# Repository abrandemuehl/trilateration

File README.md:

# Attempted ESP8266 Based WiFi Trilateration

This was a project done for UIUC's ECE 445 - Senior Design.

This project does not trilaterate positions succesfully - code for communication is still needed.

The program writes the MAC address and the associated RSSI of packets received in promiscuous mode to the UART connection at 115200 BAUD.
The messages are in a binary format found in `common/messages.h`.
They are read back by the PC program and displayed like so
```
WIFI:   6c:72:e7:d1:12:4d 40
Serial: 6c:72:e7:d1:12:4d 40
WIFI:   6c:72:e7:d1:12:4d 40
Serial: 6c:72:e7:d1:12:4d 40
WIFI:   6c:72:e7:d1:12:4d 40
Serial: 6c:72:e7:d1:12:4d 40
WIFI:   6c:72:e7:d1:12:4d 40
Serial: 6c:72:e7:d1:12:4d 40
WIFI:   6c:72:e7:d1:12:4d 40
Serial: 6c:72:e7:d1:3f:e2 6
WIFI:   6c:72:e7:d1:3f:e2 6
Serial: 6c:72:e7:d1:3f:e2 6
WIFI:   6c:72:e7:d1:3f:e2 6
Serial: 40:78:e7:d1:3f:e2 6
WIFI:   40:78:e7:d1:3f:e2 6
Serial: 2c:78:e7:d1:3f:e2 6
```
Messages prefaced with `WiFi` were received by the incomplete communication code.
The `Serial` came from the ESP8266.

There are some useful code snippets that can be used in other ESP8266 based projects.
The hardware design files also might be somewhat useful for reference.

The original goal of the project was to create a way to track WiFi devices indoors.
Our strategy was to enter promiscuous mode, and look at the RSSI of received packets, and use that to estimate the distance of the transmitting device from the ESP.

Boards were designed as part of the requirements for the class, but they are almost hardware equivalent to most simple ESP modules that you can purchase online for a lower price...
Also, the boards that we created have problems that we couldn't track down. We're pretty sure they were caused by poor fabrication, but there may be some flaw in the original designs.

## Building and running

Note: These instructions are for linux only.
We ran into issues with the toolchain on Mac that had to do with the size of the binary created not fitting into iram.

First, clone with the submodules included
```bash
$ git clone --recursive https://github.com/abrandemuehl/trilateration.git
```
Or, if you've already cloned it without submodules, use
```bash
$ git submodule update --init --recursive
```

Then, edit the makefile for the submodule [esp-open-sdk](https://github.com/pfalcon/esp-open-sdk) to use the 0.9.4 version.
This can be done by editing the line that says
```
VENDOR_SDK = x.x.x
```
to be
```
VENDOR_SDK = 0.9.4
```
then run `make` in the esp/esp-open-sdk directory. (This step takes a while)

Once that is complete, you can build the main app.

First, create a directory to hold the binary files `mkdir esp/bin`.

To build the main application, you first have to `source .env` to get the paths of the toolchain commands.
Once you've done that, run `make` in the `esp` directory.

Then you can run `make flash` to use the esptool to flash it onto the ESP8266 module of your choice that is in program mode.

## Strategy
Trilateration is a pretty simple concept.
You have 3 spheres in space with known radii, and you want to find the intersection point of all of the surfaces of the spheres.
You can use this strategy to get the location of a point, given the centers and radii of 3 spheres where the point lies on their surfaces.

See the [wikipedia](https://en.wikipedia.org/wiki/Trilateration) article and [this stackoverflow question](http://stackoverflow.com/questions/16176656/trilateration-and-locating-the-point-x-y-z) for more information about the algorithm.

The exact trilateration algorithm is implemented in `common/trilatertion.c`.

## ESP Specific Code

#### Promiscuous mode and MAC addresses
In order to use communicate the positions and radii of the circles estimated from the RSSI, each device must be identifiable through some means.
We chose the MAC address of devices, as this is *supposed* to be unique per device.
However, the information given to the promiscuous_rx_cb by the SDK is very limited on SDK versions >= 0.9.5.
It only passes some basic information about the packet to the callback, which does not include anything that can be used to identify the sender.
I'm not sure why they removed this functionality, but it exists in the SDK version 0.9.4, so we chose to use it.

When using SDK 0.9.4, we can get the whole 802.11 header of the packet, making it easy to get the MAC address of the sender and destination devices.
The basic structure of 802.11 packets is shown in `esp/network_80211.h` which we modified from the version found at https://github.com/ly0/esp8266-smartlink.
We added the structure of data frames, since that was what we wanted to use.

#### STATION mode and Promiscuous mode
The big problem we ran into with promiscuous mode was that the ESP must be in STATION mode for promiscuous mode to work.
This was a problem for our original design, since we planned to use the mesh networking capabilities of the ESP to communicate the positions and radii of the circles used for trilateration.

#### `rst cause:4`
Another problem we found was that the promiscuous mode callback runs at a high priority.
So, when you get more packets than you can process, the promiscuous callback will starve some other important task in the SDK (not sure which one) and cause a watchdog timer to reset the device.
The reset will cause the device to write `rst cause:4, boot mode: (x, x)` to the UART connection.
The `cause:4` indicates that the reset was caused by a watchdog timer going off, as documented [here](http://www.esp8266.com/viewtopic.php?p=2096#p2112).

The only way to mitigate this reset problem is to do less work in the promiscuous mode callback.
This doesn't mean you have to do less work total, you just need to delegate it to a lower priority task.

In the ESP sdk, tasks can be defined with the following lines of code
```C
#define message_procTaskPrio        1
#define message_procTaskQueueLen    2
os_event_t message_procTaskQueue[message_procTaskQueueLen];
static void message_procTask(os_event_t *event);

void ICACHE_FLASH_ATTR
user_init() {
  ...
  // Defines a task that can be started with system_os_post
  system_os_task(message_procTask, message_procTaskPrio,
                 message_procTaskQueue, message_procTaskQueueLen);
  ...
}
```

This defines, the task, but doesn't run it.
To run a task, run system_os_post in your promicuous mode callback.
```
void ICACHE_FLASH_ATTR
promisc_cb(uint8_t *buf, uint16_t len) {
  ...
  system_os_post(message_procTaskPrio, 0, 0);
  ...
}
```
When `system_os_post` is called, it will queue up the message processing task to be run once the CPU frees up from all of the system tasks that run at higher priority.

How you pass data to this task is up to you.
I used a ring buffer, but I didn't make it thread safe, so there are race conditions in there.

## PC Code

The PC code was added because of the STATION mode problem with promiscuous mode.
Without access points to connect to, each board would not be able to communicate with the other ones, making trilateration impossible.
We didn't want to require that the devices connect to a network, so we planned to send messages over USB to a laptop, then have the laptop broadcast the values.
We ran out of time before we could test if this method would work.

## Trilateration Problems
The trilateration algorithm and code that we had intended to use would not with real values based on RSSI.
The algorithm solves a system of equations using the spheres, but only finds a solution if they intersect at only one point.
This is not a good algorithm because it doesn't find a solution when the estimated spheres don't exactly line up, which won't happen in almost all cases.

## In conclusion

We ran out of time and couldn't finish the project for the class.
We have no intentions of working on this code again, but if you have any questions about the choices made in the code, feel free to open an issue.

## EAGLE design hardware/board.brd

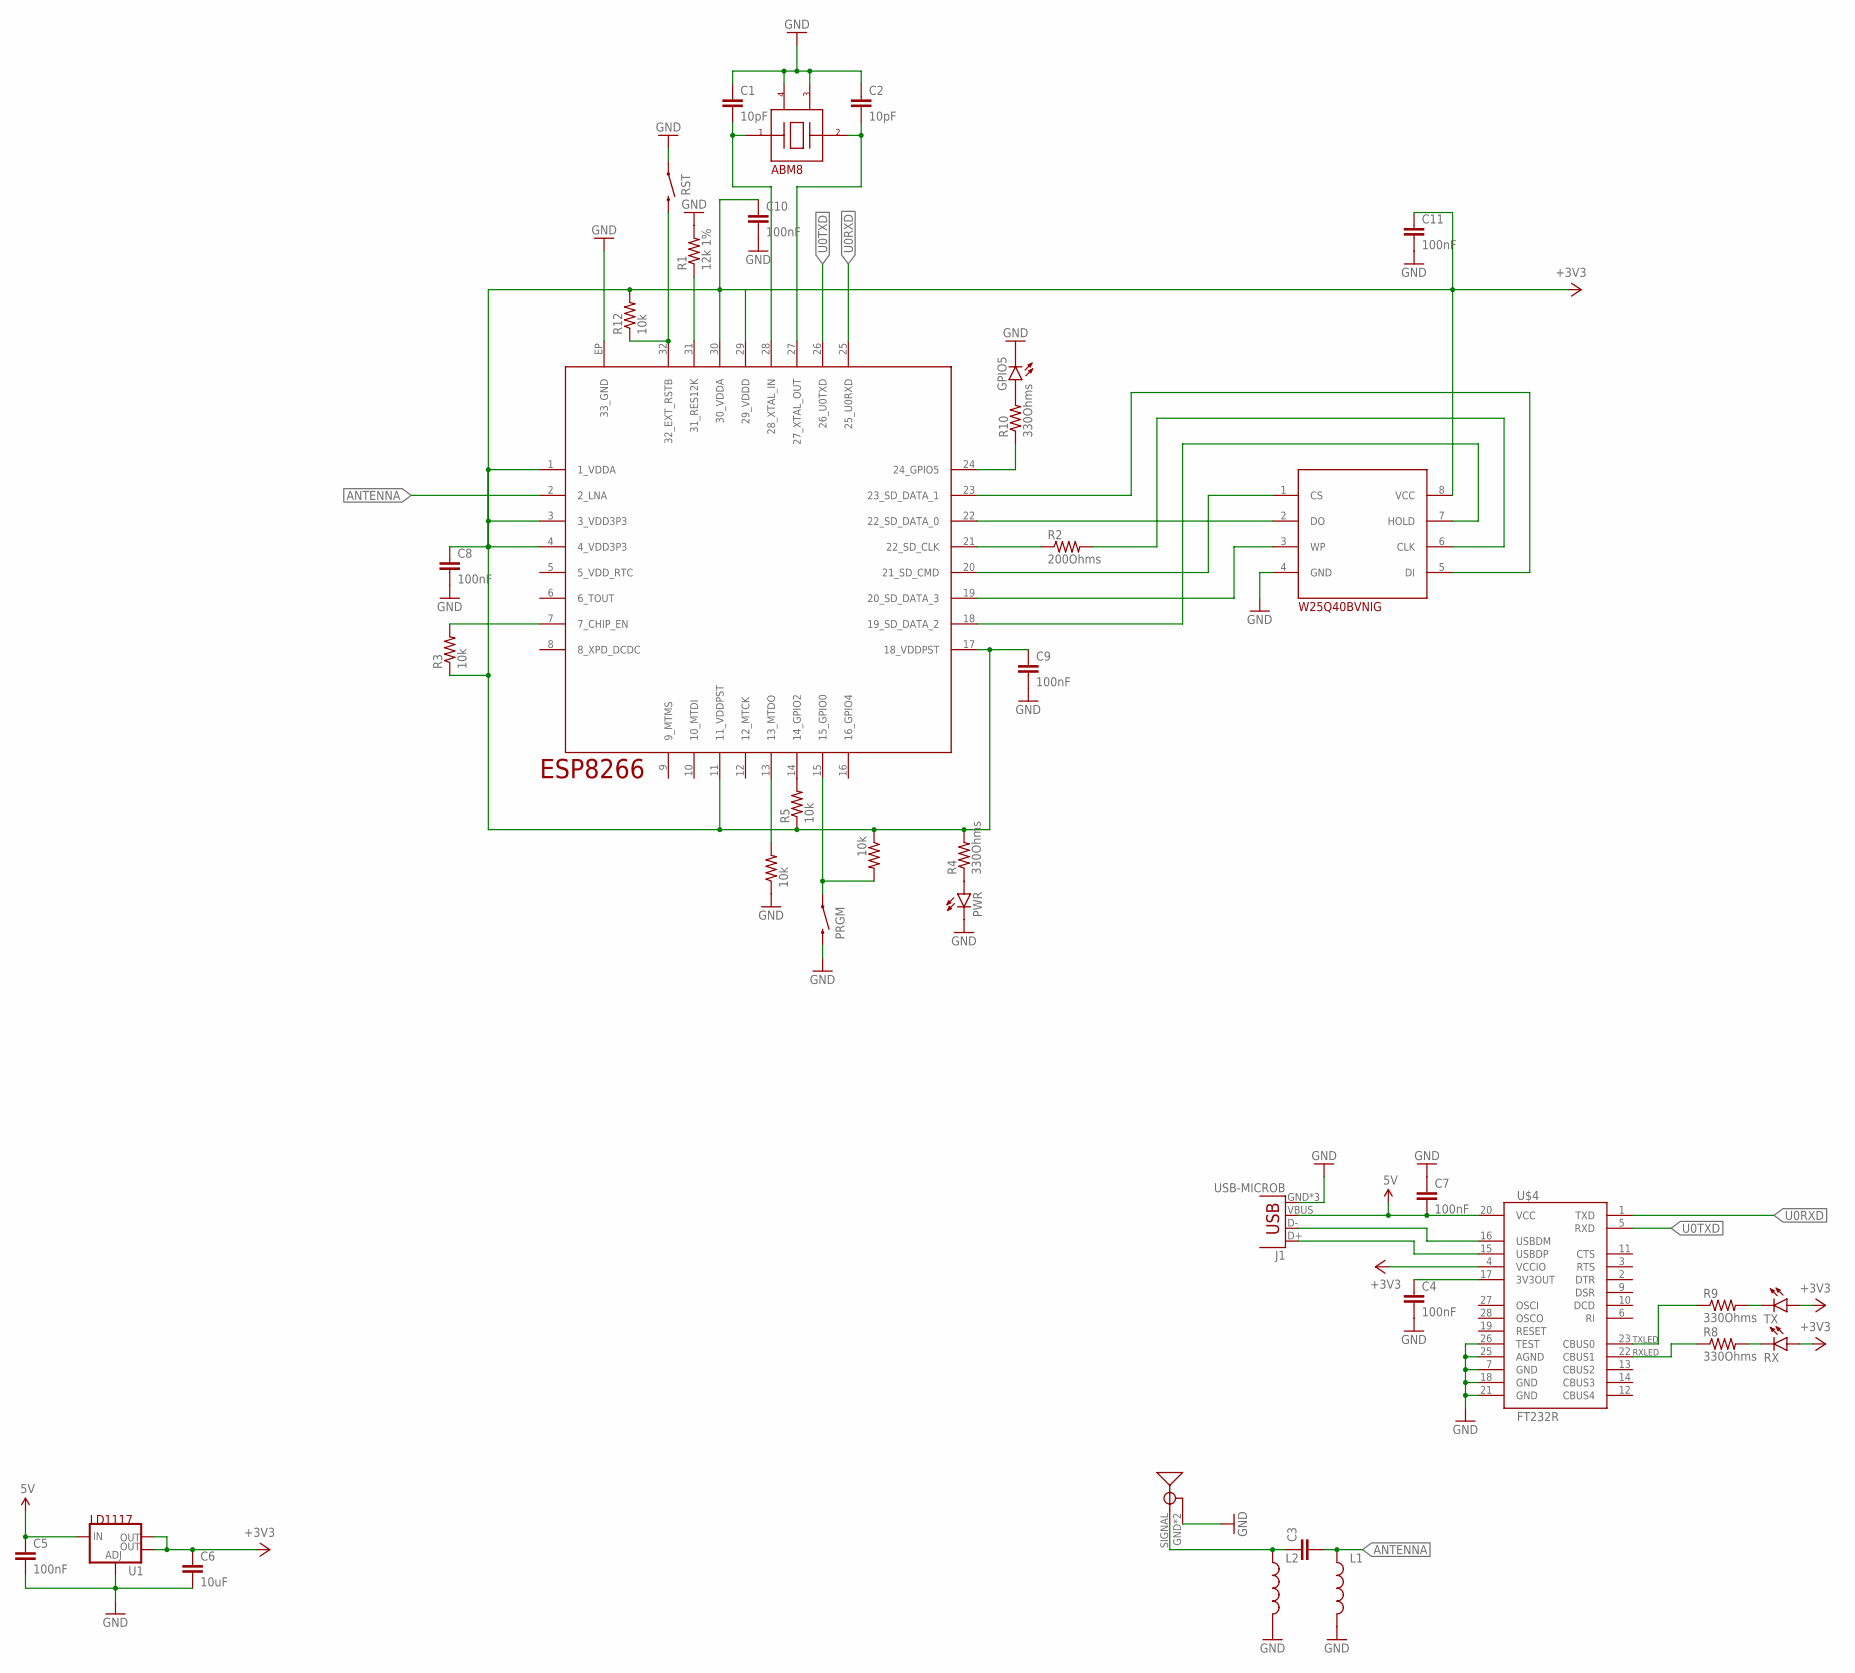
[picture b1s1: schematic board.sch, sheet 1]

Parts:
C1, C2: 10pF; 0603-CAP
C3: CAP0402-CAP; 0402-CAP
C4, C5, C7, C8, C9, C10, C11: 100nF; 0603-CAP
C6: 10uF; 0603-CAP
GPIO5: LED0603; LED-0603
J1: USB-MICROB
L1, L2: INDUCTOR0402; C0402
PRGM: SWITCH-MOMENTARY-2PTH; TACTILE-PTH
PWR: LED0603; LED-0603
R1: 12k 1%; 0603-RES
R2: 200Ohms; 0402-RES
R3, R5, R6, R7, R12: 10k; 0603-RES
R4, R8, R9, R10: 330Ohms; 0603-RES
RST: SWITCH-MOMENTARY-2PTH; TACTILE-PTH
RX: LED0603; LED-0603
TX: LED0603; LED-0603
U1: V_REG_LM1117SOT223; SOT223
U$1: W25Q40BVNIG; SOIC-8
U$2: ESP8266; QFN-32
U$3: ABM8
U$4: FT232R; SSOP-28
U$5: OMNIANTENNA; ANTENNA

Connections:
+3V3: C6.1, C8.1, C9.1, C10.1, C11.1, R3.1, R4.2, R5.1, R6.1, R12.2, RX.A, TX.A, U1.2 (OUT), U1.4 (OUT), U$1.8 (VCC), U$2.1 (1_VDDA), U$2.3 (3_VDD3P3), U$2.4 (4_VDD3P3), U$2.11 (11_VDDPST), U$2.17 (18_VDDPST), U$2.29 (29_VDDD), U$2.30 (30_VDDA), U$4.4 (VCCIO)
ANTENNA: C3.2, L1.1, U$2.2 (2_LNA)
GND: C1.1, C2.1, C4.2, C5.2, C6.2, C7.1, C8.2, C9.2, C10.2, C11.2, GPIO5.C, J1.GND, J1.MT1 (GND), J1.MT2 (GND), L1.2, L2.2, PRGM.3 (2), PWR.C, R1.2, R7.1, RST.1, U1.1 (ADJ), U$1.4 (GND), U$2.EP (33_GND), U$3.P$2 (GND), U$3.P$4 (GND2), U$4.7 (GND), U$4.18 (GND), U$4.21 (GND), U$4.25 (AGND), U$4.26 (TEST), U$5.GND, U$5.GND1 (GND)
unnamed: R2.2, U$1.6 (CLK)
unnamed: U$1.2 (DO), U$2.22 (22_SD_DATA_0)
unnamed: U$1.5 (DI), U$2.23 (23_SD_DATA_1)
unnamed: U$1.7 (HOLD), U$2.18 (19_SD_DATA_2)
unnamed: R1.1, U$2.31 (31_RES12K)
unnamed: U$1.3 (WP), U$2.19 (20_SD_DATA_3)
unnamed: U$1.1 (CS), U$2.20 (21_SD_CMD)
unnamed: R2.1, U$2.21 (22_SD_CLK)
unnamed: C3.1, L2.1, U$5.SIGNAL
unnamed: R3.2, U$2.7 (7_CHIP_EN)
unnamed: PWR.A, R4.1
unnamed: R5.2, U$2.14 (14_GPIO2)
unnamed: C4.1, U$4.17 (3V3OUT)
unnamed: R7.2, U$2.13 (13_MTDO)
unnamed: J1.D+, U$4.15 (USBDP)
unnamed: J1.D-, U$4.16 (USBDM)
unnamed: R8.1, U$4.22 (CBUS1)
unnamed: R9.1, U$4.23 (CBUS0)
unnamed: R9.2, TX.C
unnamed: PRGM.1, R6.2, U$2.15 (15_GPIO0)
unnamed: GPIO5.A, R10.2
unnamed: R10.1, U$2.24 (24_GPIO5)
unnamed: R12.1, RST.3 (2), U$2.32 (32_EXT_RSTB)
RX: R8.2, RX.C
U0RXD: U$2.25 (25_U0RXD), U$4.1 (TXD)
U0TXD: U$2.26 (26_U0TXD), U$4.5 (RXD)
VUSB: C5.1, C7.2, J1.VBUS, U1.3 (IN), U$4.20 (VCC)
XTAL_IN: C1.2, U$2.28 (28_XTAL_IN), U$3.P$1 (IN)
XTAL_OUT: C2.2, U$2.27 (27_XTAL_OUT), U$3.P$3 (OUT)

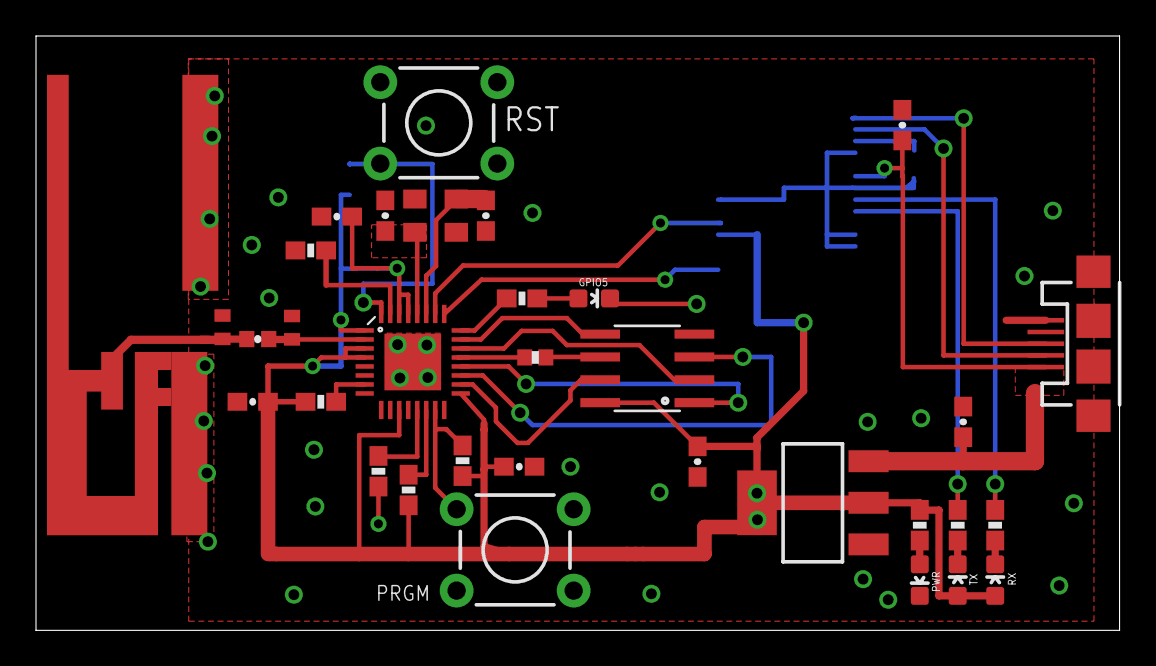
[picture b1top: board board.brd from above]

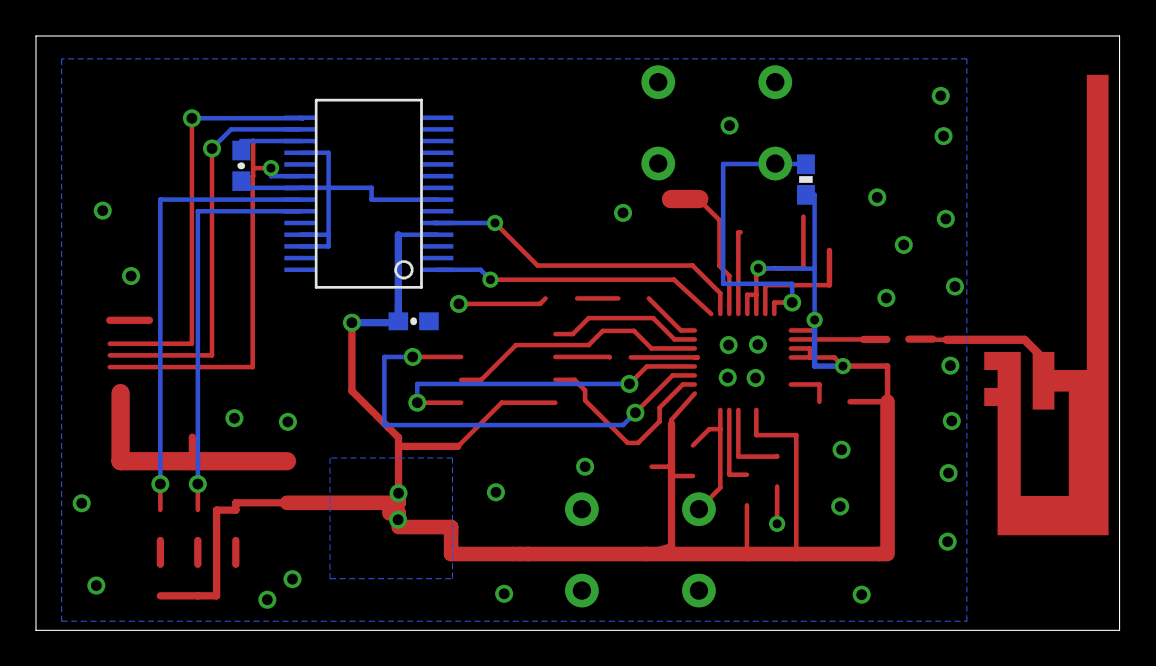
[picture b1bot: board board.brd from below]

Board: 2 copper layers, 60.2 x 33.0 mm, 37 parts (4 on the bottom side), 32 nets.

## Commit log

2016-11-22 Add 3d trilateration code. Does not handle non exact radii
2016-11-24 Add arduino code
2016-11-29 Sniffing Code
    Only compatible with the 0.9.4 SDK
2016-11-29 UART driver files
2016-11-30 not compiling (overflowing)
2016-11-30 Part time commit
2016-11-30 comms
2016-12-05 Fix comment
2016-12-11 Add hardware design files
2016-12-11 Cleanup the repo for public viewing
2016-12-11 Add README

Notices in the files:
parts and their libraries:
SparkFun-Capacitors: Licensing: Creative Commons ShareAlike 4.0 International - https://creativecommons.org/licenses/by-sa/4.0
